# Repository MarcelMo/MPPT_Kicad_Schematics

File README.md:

Based on https://www.instructables.com/DIY-1kW-MPPT-Solar-Charge-Controller/
Since I wanted to be able to change the board layout and to test KiCad I decided to give this "conversion" a try.

- I removed the keyboard pullups, they are not needed when activating the internal pullup. And I prefer switching to ground anyway, so I can use 5V for the display and the keyboard.
- I changed the footprint of the screw terminals, since I did not find any other (trustworthy) 50A capable terminal. https://www.degson.com/content/details_552_880568.html
- Added JTAG interface
- Added a SD card and IIC socket, mainly for a RTC module. Should allow for much better offline logging.
- Switched to 1.27mm pitch smd connector. No need for 2.54mm. Just uses up too much space - on both sides of the board. Also added a few spare IOs and IIC.
- Fan driver transistor. ToDo: Maybe better switch +, and not GND. Although switching ground allows for more flexibility regarding fan voltage.
- Had to divide GND into GND and GND2, so I could add the GND copper bar to the schematics and the layout without getting too hacky... Found no better "KiCad way"
- 3D models are almost complete. SD card is not perfect.
- Switched to USB-C

3D VRML preview: https://marcelmo.github.io/MPPT_Kicad_Schematics/ (Thanks to https://easyw.github.io/vrm360/ )

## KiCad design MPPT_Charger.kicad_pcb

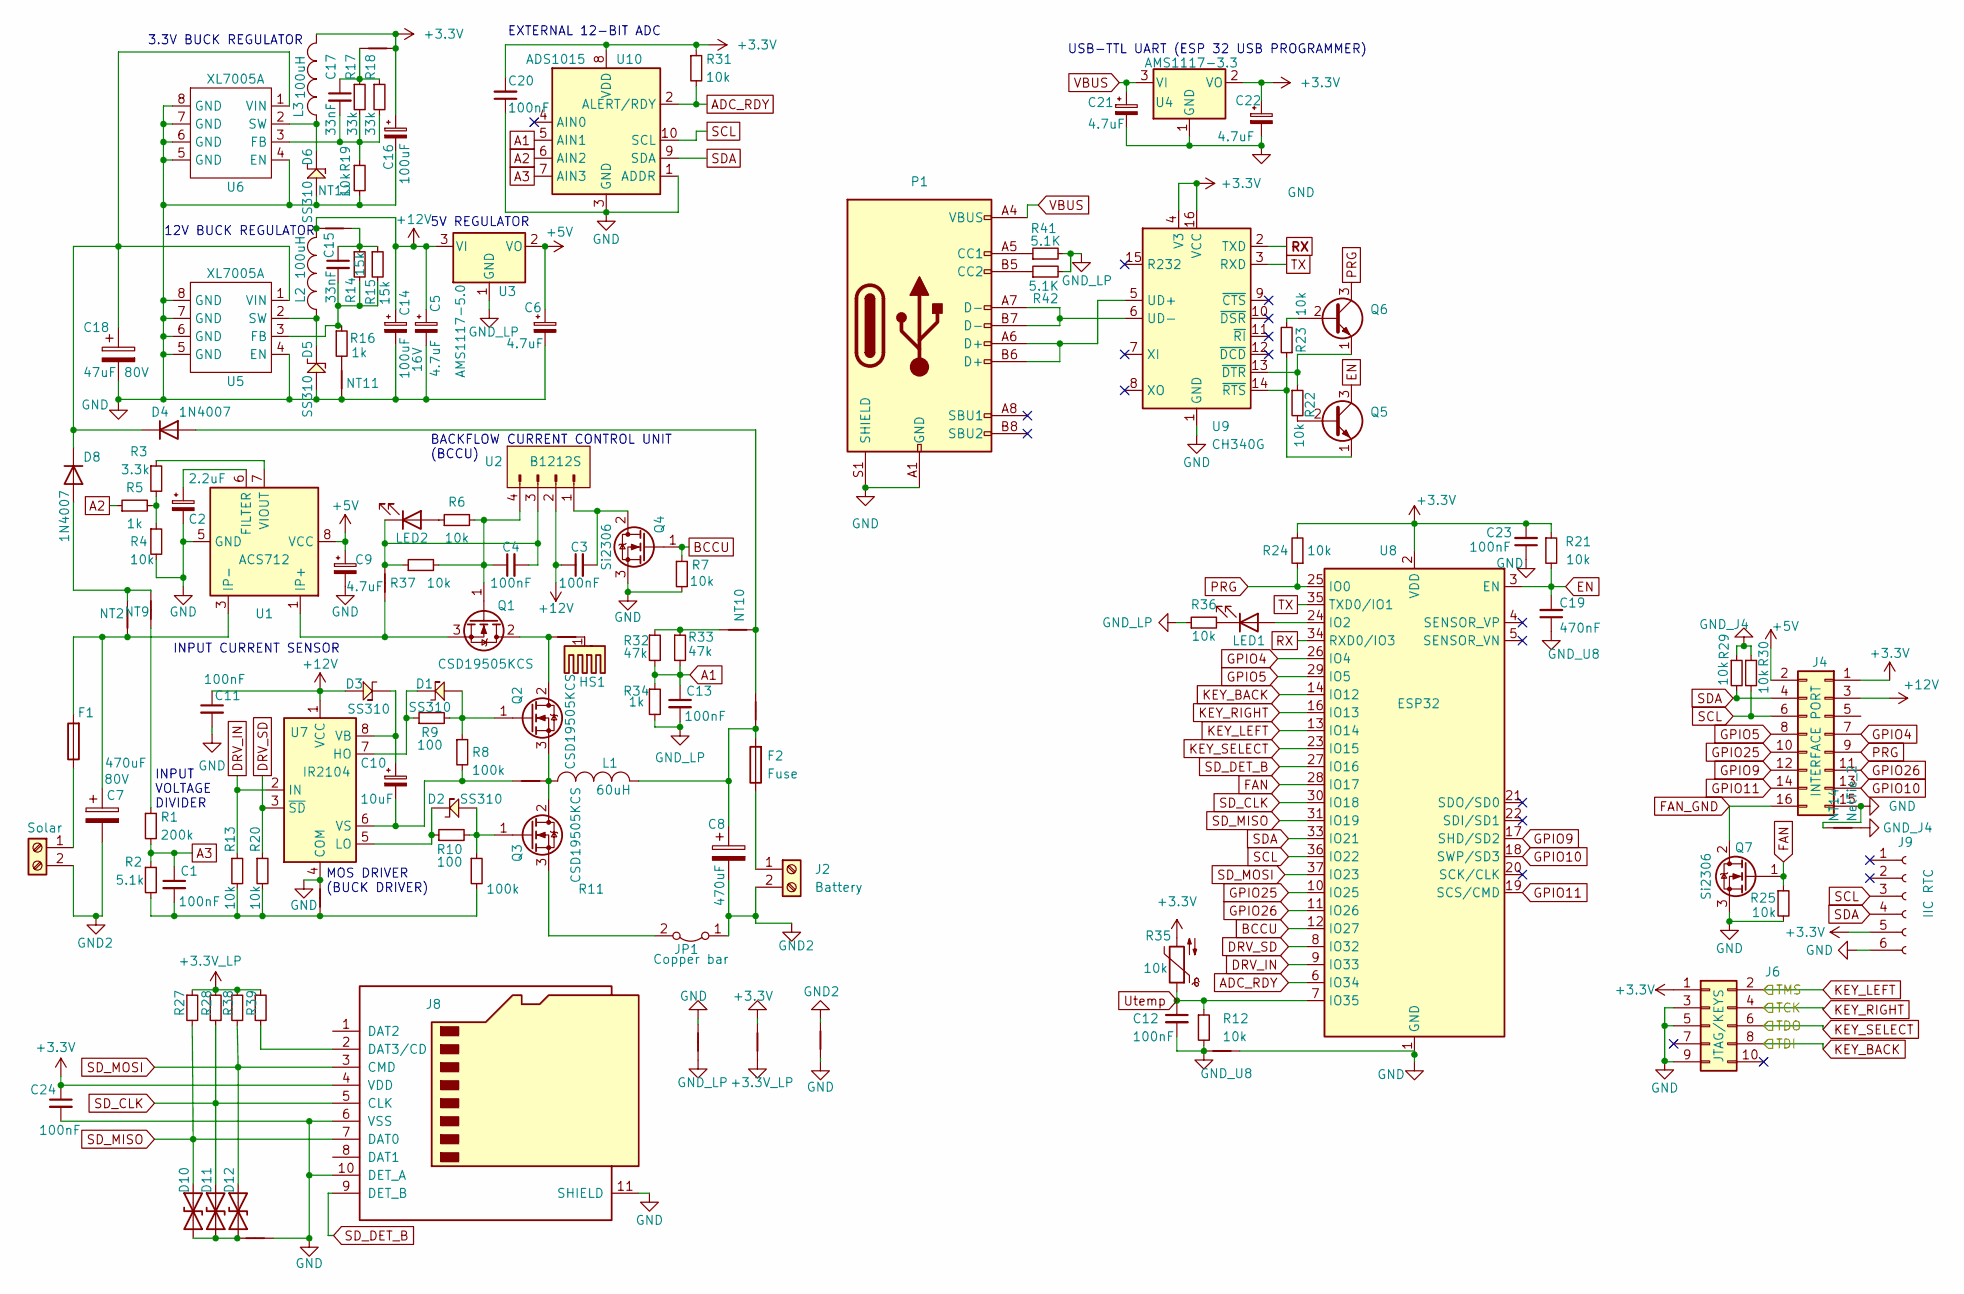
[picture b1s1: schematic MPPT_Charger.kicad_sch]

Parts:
C1: 100nF; C_0603_1608Metric; JLCPCB Part C14663 CC0603KRX7R9BB104
C2: 2.2uF; C_0603_1608Metric
C3, C4, C11, C12, C13, C20, C23, C24: 100nF; C_0603_1608Metric
C5, C9, C21, C22: 4.7uF; C_0805_2012Metric
C6: 4.7uF; C_0805_2012Metric; Voltage 5V; LCSC C1779 CL21A475KAQNNNE
C7: 470uF; CP_Radial_D16.0mm_P7.50mm; Voltage 80V
C8: 470uF; CP_Radial_D16.0mm_P7.50mm; Voltage 50V
C10: 10uF; CP_EIA-3216-10_Kemet-I
C14: 100uF; C_Elec_6.3x5.8; Voltage 16V
C15: 33nF; C_0603_1608Metric
C16: 100uF; C_Elec_6.3x5.8
C17: 33nF; C_0603_1608Metric; Voltage 5V; LCSC C21117 CL10B333KB8NNNC
C18: 47uF; CP_Elec_10x10.5; Voltage 80V
C19: 470nF; C_0603_1608Metric
D1, D2, D3, D5, D6: SS310; D_SMB
D4, D8: 1N4007; D_SOD-123F
D10, D11, D12: LESD8D3.3CAT5G; SOD882D.kicad_mod
F1, F2: Fuse; Fuse_Blade_ATO_directSolder
HS1: Heatsink_Pad; Heatsink_125x35x50mm_3xFixationM3
J1: Solar; TerminalBlock_DEGSON_DG135T
J2: Battery; TerminalBlock_DEGSON_DG135T
J4: INTERFACE PORT; PinHeader_2x08_P1.27mm_Vertical_SMD
J6: JTAG/KEYS; PinHeader_2x05_P1.27mm_Vertical_SMD
J8: Micro_SD_Card_Det_Hirose_DM3AT; microSD_HC_Molex_104031-0811
J9: IIC RTC; PinHeader_1x06_P2.54mm_Vertical
JP1: Copper bar; COPPER_BAR
L1: 60uH; L_Toroid_Vertical_L21.6mm_W11.4mm_P7.62mm_Pulse_KM-3
L2, L3: 100uH; L_TracoPower_TCK-047_5.2x5.8mm
LED1, LED2: LED; LED_0805_2012Metric
NT1: GND to GND2; NetTie-2_SMD_Pad0.5mm
NT2, NT4, NT5, NT6, NT9, NT10, NT11, NT12, NT13, NT14, NT15, NT16, NT17: NetTie_2; NetTie-2_SMD_Pad0.5mm
NT3, NT7, NT8: NetTie-2_SMD_Pad0.5mm
P1: USB_C_Receptacle_USB2.0_16P; USB_C_Receptacle_GCT_USB4105-xx-A_16P_TopMnt_Horizontal
Q1, Q2: CSD19505KCS; TO-220-3_Vertical
Q3: CSD19505KCS; Package_TO_SOT_THTTO-220-3_Vertical_Insulated
Q4, Q7: Si2306; SOT-23
Q5, Q6: MMBT3904 1A; SOT-23
R1: 200k; R_0603_1608Metric
R2: 5.1k; R_0603_1608Metric
R3: 3.3k; R_0603_1608Metric
R4, R6, R7, R12, R13, R19, R20, R21, R22, R23, R24, R25, R27, R28, R29, R30, R31, R36, R37, R38, R39: 10k; R_0603_1608Metric
R5, R16, R34: 1k; R_0603_1608Metric
R8, R11: 100k; R_0603_1608Metric
R9, R10: 100; R_0603_1608Metric
R14, R15: 15k; R_0603_1608Metric
R17, R18: 33k; R_0603_1608Metric
R32, R33: 47k; R_0603_1608Metric
R35: 10k; PinHeader_1x02_P2.54mm_Vertical
R41, R42: 5.1K; R_0603_1608Metric
U1: ACS712; SOIC-8_3.9x4.9mm_P1.27mm; LCSC C10681 ACS712ELCTR-20A-T
U2: B1212S
U3: AMS1117-5.0; SOT-223-3_TabPin2
U4: AMS1117-3.3; SOT-223-3_TabPin2
U5, U6: XL7005A; SOIC-8-1EP_3.9x4.9mm_P1.27mm_EP2.29x3mm_ThermalVias
U7: IR2104; SOIC-8_3.9x4.9mm_P1.27mm
U8: ESP32; ESP32-WROOM-32
U9: CH340G; SOIC-16_3.9x9.9mm_P1.27mm; LCSC C14267 CH340G
U10: ADS1015; TSSOP-10_3x3mm_P0.5mm

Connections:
+3.3V: C16.1, C20.2, C22.1, C23.2, C24.1, J4.1, J6.1, J8.4 (VDD), J9.5, L3.2, NT8.2, NT13.2, R21.1, R24.2, R31.1, R35.2, U4.2 (VO), U8.2 (VDD), U9.4 (V3), U9.16 (VCC), U10.8 (VDD)
+3.3V_LP: NT8.1, R27.1, R28.1, R38.1, R39.1
+5V: C6.1, C9.1, J4.2, U1.8 (VCC), U3.2 (VO)
+12V: C3.1, C5.1, C11.1, C14.1, D3.1 (Katode), J4.3, L2.2, NT12.1, U2.2 (VIN), U3.3 (VI), U7.1 (VCC)
A1: C13.1, R32.2, R33.2, R34.1, U10.5 (AIN1)
A2: R5.1, U10.6 (AIN2)
A3: C1.1, R1.2, R2.1, U10.7 (AIN3)
ADC_RDY: R31.2, U8.6 (IO34), U10.2 (ALERT/RDY)
BCCU: Q4.1 (G), R7.1, U8.12 (IO27)
DRV_IN: R13.1, U7.2 (IN), U8.9 (IO33)
DRV_SD: R20.1, U7.3 (~SD), U8.8 (IO32)
EN: C19.2, Q5.3 (C), R21.2, U8.3 (EN)
FAN: Q7.1 (G), R25.1, U8.28 (IO17)
FAN_GND: J4.16, Q7.2 (D)
GND: C2.2, C5.2, C6.2, C9.2, C11.2, C14.2, C16.2, C18.2, C20.1, C21.2, C22.2, C23.1, C24.2, D5.1 (Katode), D6.1 (Katode), J4.15, J6.3, J6.5, J6.9, J8.6 (VSS), J8.10 (DET_A), J8.11 (SHIELD), J9.6, NT1.2, NT7.2, NT11.1, NT14.2, NT15.2, NT16.2, NT17.2, P1.A1 (GND), P1.A12 (GND), P1.B1 (GND), P1.B12 (GND), P1.S1 (SHIELD), Q4.3 (S), Q7.3 (S), R4.2, R7.2, R19.2, R25.2, U1.5 (GND), U4.1 (GND), U5.4 (EN), U5.5 (GND), U5.6 (GND), U5.7 (GND), U5.8 (GND), U6.4 (EN), U6.5 (GND), U6.6 (GND), U6.7 (GND), U6.8 (GND), U7.4 (COM), U8.1 (GND), U8.15 (GND), U8.38 (GND), U8.39 (GND), U9.1 (GND), U10.1 (ADDR), U10.3 (GND)
GND2: C7.2, C8.2, J1.2, J2.2, JP1.1 (A), NT1.1
GND_J4: NT14.1, R29.1, R30.1
GND_LP: C13.2, NT7.1, R34.2, R36.1, R41.2, R42.2, U3.1 (GND)
GND_U8: C12.2, C19.1, NT15.1, R12.2
GPIO4: J4.7, U8.26 (IO4)
GPIO5: J4.8, U8.29 (IO5)
GPIO9: J4.12, U8.17 (SHD/SD2)
GPIO10: J4.13, U8.18 (SWP/SD3)
GPIO11: J4.14, U8.19 (SCS/CMD)
GPIO25: J4.10, U8.10 (IO25)
GPIO26: J4.11, U8.11 (IO26)
KEY_BACK: J6.8, U8.14 (IO12)
KEY_LEFT: J6.2, U8.13 (IO14)
KEY_RIGHT: J6.4, U8.16 (IO13)
KEY_SELECT: J6.6, U8.23 (IO15)
unnamed: C1.2, NT17.1, R2.2, R11.2, R13.2, R20.2
unnamed: C7.1, F1.2, NT2.2, U1.3 (IP-), U1.4 (IP-)
unnamed: C8.1, F2.2, L1.2, NT6.1
unnamed: C15.1, NT12.2, R14.1, R15.1
unnamed: C17.1, NT13.1, R17.1, R18.1
unnamed: D1.2 (Anode), R9.1, U7.7 (HO)
unnamed: D1.1 (Katode), Q2.1 (G), R8.1, R9.2
unnamed: D2.2 (Anode), R10.1, U7.5 (LO)
unnamed: D2.1 (Katode), Q3.1 (G), R10.2, R11.1
unnamed: C10.1, D3.2 (Anode), U7.8 (VB)
unnamed: D4.2 (A), NT6.2, NT10.1
unnamed: C18.1, D4.1 (K), D8.1 (K), U5.1 (VIN), U6.1 (VIN)
unnamed: D5.2 (Anode), L2.1, U5.2 (SW)
unnamed: D6.2 (Anode), L3.1, U6.2 (SW)
unnamed: D8.2 (A), NT2.1, NT9.1
unnamed: D10.1 (A1), D11.1 (A1), D12.1 (A1), NT16.1
unnamed: F1.1, J1.1
unnamed: F2.1, J2.1
unnamed: J8.2 (DAT3/CD), R39.2
unnamed: JP1.2 (B), Q3.3 (S)
unnamed: LED1.2 (A), U8.24 (IO2)
unnamed: LED1.1 (K), R36.2
unnamed: LED2.2 (A), R6.1
unnamed: C4.2, LED2.1 (K), NT3.2, R37.1, U2.3 (GND2)
unnamed: HS1.1, NT5.1
unnamed: NT9.2, R1.1
unnamed: NT10.2, R32.1, R33.1
unnamed: NT11.2, R16.2
unnamed: P1.A5 (CC1), R41.1
unnamed: P1.B5 (CC2), R42.1
unnamed: NT5.2, Q1.2 (D), Q2.2 (D)
unnamed: C4.1, Q1.1 (G), R6.2, R37.2, U2.4 (VOUT)
unnamed: NT3.1, Q1.3 (S), U1.1 (IP+), U1.2 (IP+)
unnamed: L1.1, NT4.2, Q2.3 (S), Q3.2 (D)
unnamed: C3.2, Q4.2 (D), U2.1 (GND)
unnamed: Q5.2 (B), R22.2
unnamed: Q5.1 (E), R23.1, U9.14 (~RTS)
unnamed: Q6.2 (B), R23.2
unnamed: Q6.1 (E), R22.1, U9.13 (~DTR)
unnamed: R3.2, R4.1, R5.2
unnamed: C2.1, U1.6 (FILTER)
unnamed: R3.1, U1.7 (VIOUT)
unnamed: C15.2, R14.2, R15.2, R16.1, U5.3 (FB)
unnamed: C17.2, R17.2, R18.2, R19.1, U6.3 (FB)
unnamed: C10.2, NT4.1, R8.2, U7.6 (VS)
unnamed: P1.A6 (D+), P1.B6 (D+), U9.5 (UD+)
unnamed: P1.A7 (D-), P1.B7 (D-), U9.6 (UD-)
PRG: J4.9, Q6.3 (C), R24.1, U8.25 (IO0)
RX: U8.34 (RXD0/IO3), U9.2 (TXD)
SCL: J4.6, J9.3, R30.2, U8.36 (IO22), U10.10 (SCL)
SDA: J4.4, J9.4, R29.2, U8.33 (IO21), U10.9 (SDA)
SD_CLK: D11.2 (A2), J8.5 (CLK), R28.2, U8.30 (IO18)
SD_DET_B: J8.9 (DET_B), U8.27 (IO16)
SD_MISO: D10.2 (A2), J8.7 (DAT0), R27.2, U8.31 (IO19)
SD_MOSI: D12.2 (A2), J8.3 (CMD), R38.2, U8.37 (IO23)
TX: U8.35 (TXD0/IO1), U9.3 (RXD)
Utemp: C12.1, R12.1, R35.1, U8.7 (IO35)
VBUS: C21.1, P1.A4 (VBUS), P1.A9 (VBUS), P1.B4 (VBUS), P1.B9 (VBUS), U4.3 (VI)

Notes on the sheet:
EXTERNAL 12-BIT ADC
12V BUCK REGULATOR
BACKFLOW CURRENT CONTROL UNIT (BCCU)
USB-TTL UART (ESP 32 USB PROGRAMMER)
3.3V BUCK REGULATOR
5V REGULATOR
MOS DRIVER (BUCK DRIVER)
INPUT CURRENT SENSOR
INPUT VOLTAGE DIVIDER

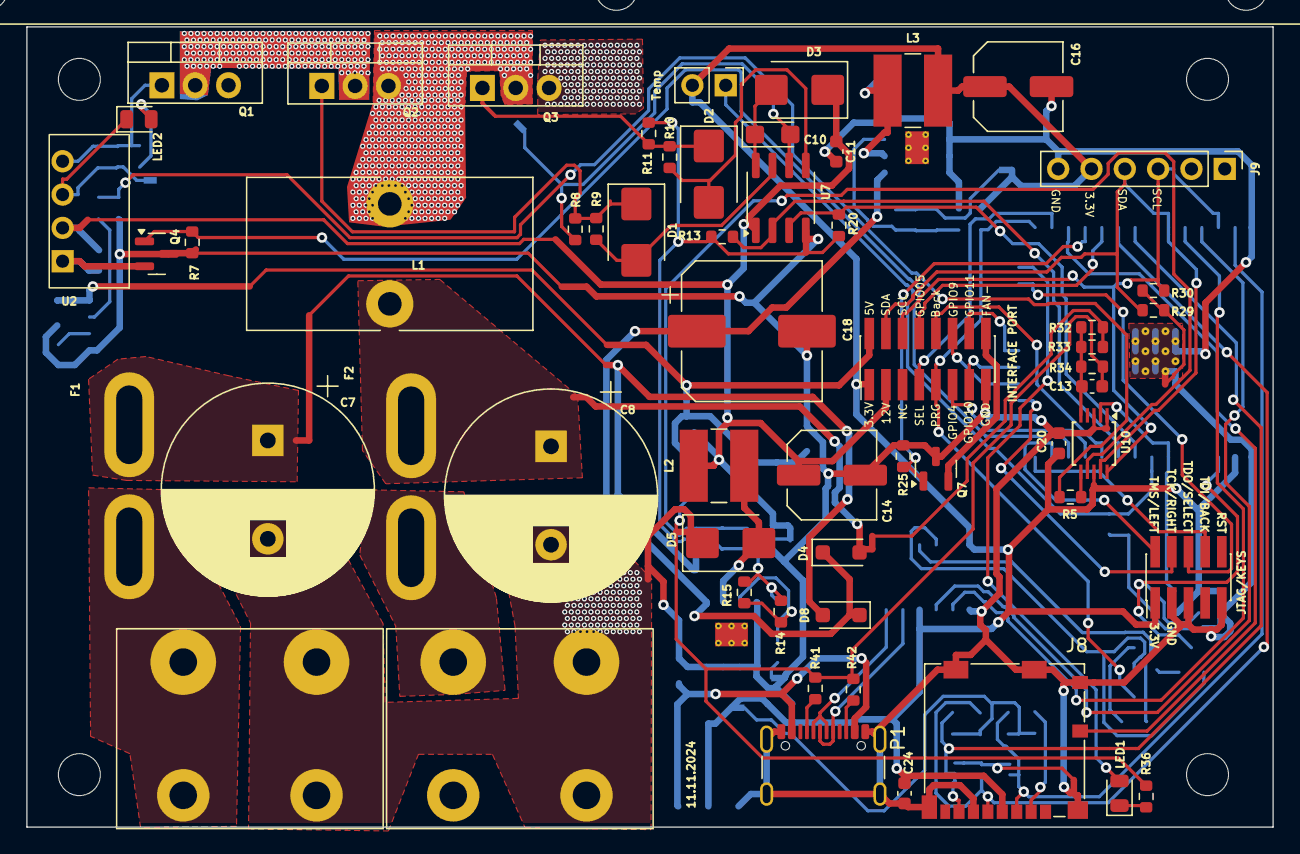
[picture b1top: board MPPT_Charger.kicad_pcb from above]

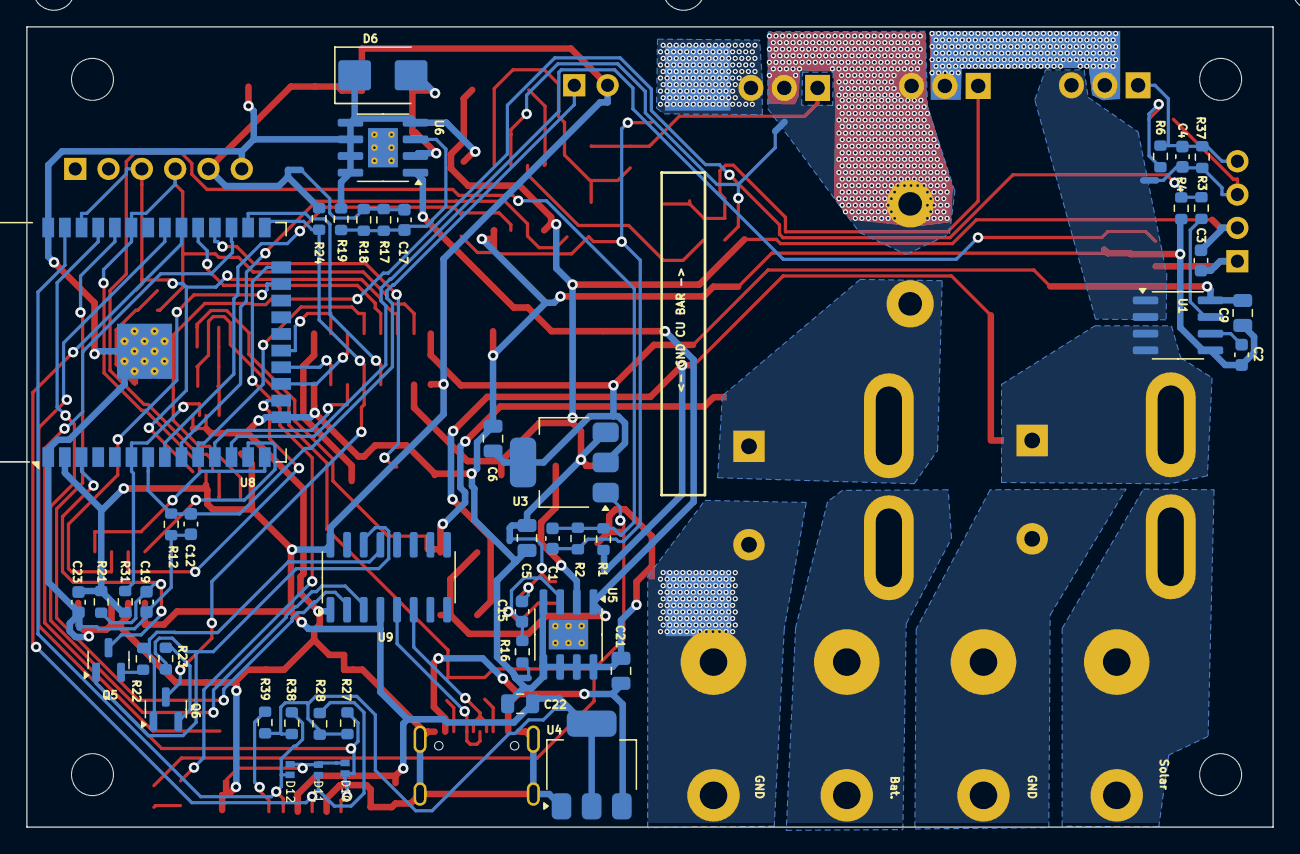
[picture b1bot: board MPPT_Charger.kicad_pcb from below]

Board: 2 copper layers, 95.0 x 61.0 mm, 127 parts (56 on the bottom side), 87 nets.

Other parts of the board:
REF1, REF2, REF3, REF4: MountingHole_3.2mm_M3

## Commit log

2022-10-11 MPPT Charger
2022-10-12 Schaltplan fertig ?
2022-10-13 Layouten...
2022-10-14 So gut wie fertig ... ?
2022-10-15 Leiterbahnen verstärkt
2022-10-16 Eigentlich okay...
2022-10-16 Fehlerhafte Pads entfernt und in Footprint eingebaut
2022-10-17 Jaaa
2022-10-17 SD + RTC
2022-10-19 3D Modelle und Footprints vervollständigt
2022-10-20 Fuse Holder 3D Modell
2022-10-21 Sieht ganz gut aus...
2022-10-22 RTC 3D Model
2022-10-22 Project renamed
2022-10-23 Heatsink and insulation ToDo: Smaller heatsink
2022-10-24 Heat sink size corrected
2022-10-25 Footprint C+R changed to 0603 where possible
2022-10-25 Done ?
2022-10-25 footprint for ADS1115 updated
2022-11-02 Holes were too small
2022-11-02 Footprint updates for some parts (mainly too small drill holes for screw terminal and larger capacitors)
2022-11-03 Footprint for 470uF was too small Some more minor changes
2022-11-03 Some parts ref was unreadable
2022-11-04 SD card pins were wrong https://github.com/MarcelMo/MPPT_Kicad_Schematics/issues/1
2022-11-05 Degson terminal 3D model path updated
2022-11-05 VRML browser preview
2022-11-05 Update .wrl path with github permalink
2022-11-05 Try 3D preview via three.js
    Anybody knows how to set the content-type to html ?
2022-11-05 Try github pages to make VRML browser preview possible
2022-11-05 VRML file path updated
2022-11-05 better not use pages of https://easyw.github.io/vrm360/ directly
2022-11-05 VRML preview in browser
    using three.js and github pages and code by https://easyw.github.io/vrm360/
    Switched project to public to use Github Pages
2022-12-20 Some missing copper and minor changes
2024-09-01 KICAD V8
2024-09-03 Reworked layout. Changed a few pins. Double power transistors removed. Traces would not be able to support the amperage anyway.
2024-09-03 3D Model Update
2024-09-23 Some manual corrections, and some too small footprints updated.
2024-10-04 A lot of updates. Used net classes. Changed some footprints and 3D models. Corrected pinouts of connectors. Changed pins for keyboard to use same pins as JTAG connector, seemed like a useful double u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
2024-10-16 Some Zones were wrong/missing
2024-10-27 USB-C corrected- I hope Moved more parts topside again
2024-11-11 RxD TxD were wrong :-(
2025-10-13 Kicad 9.0 + minor changes (some "power" vias)
